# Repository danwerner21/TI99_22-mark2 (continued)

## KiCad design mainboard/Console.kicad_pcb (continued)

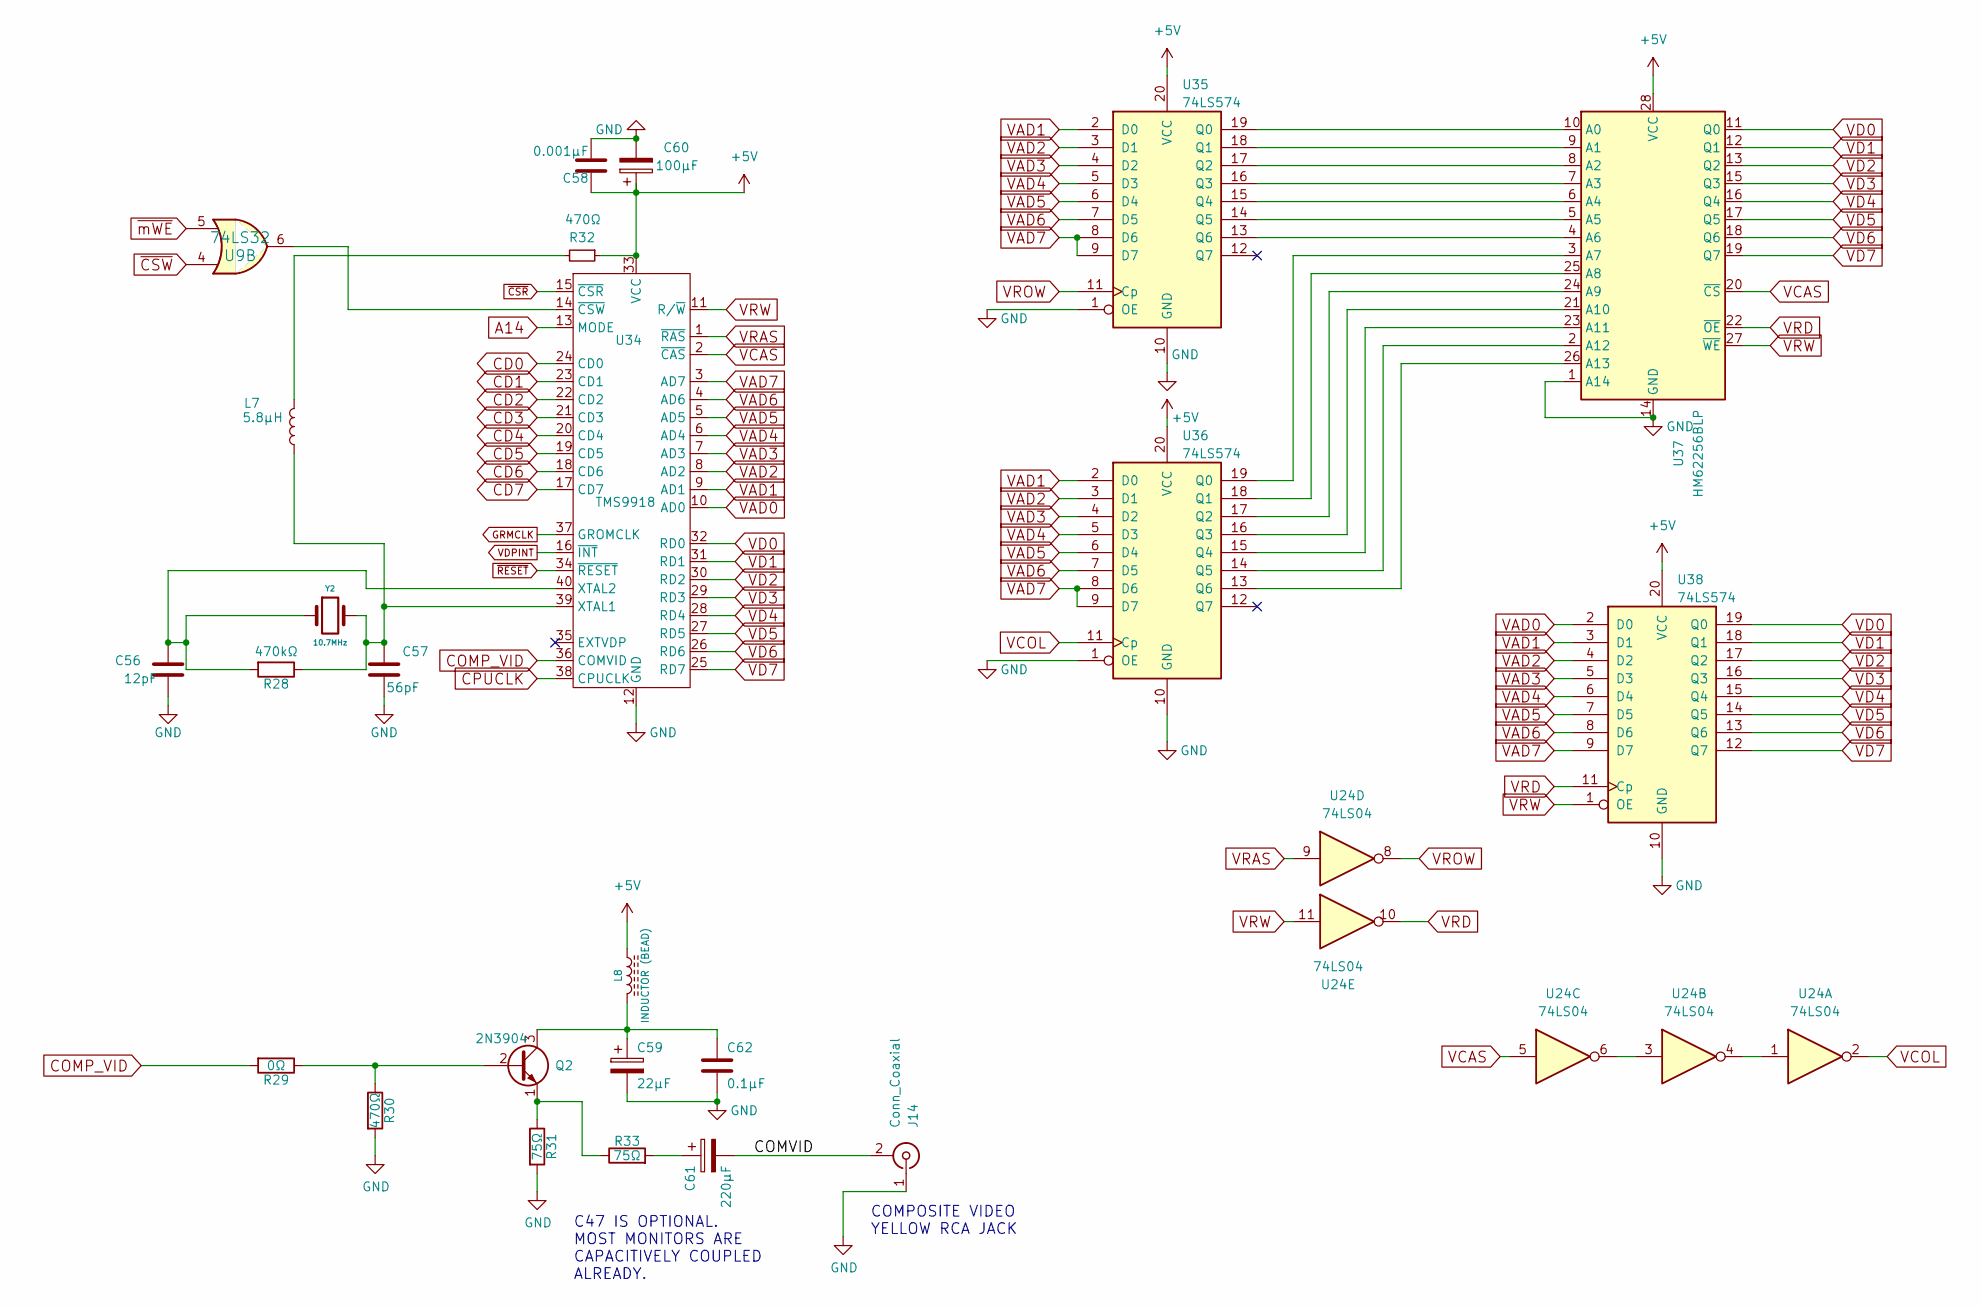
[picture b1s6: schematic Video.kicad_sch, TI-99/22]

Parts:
C56: 12pF; STD_DDW_CAP
C57: 56pF; STD_DDW_CAP
C58: 0.001µF; STD_DDW_CAP
C59: 22µF; STD_DDW_PCAP
C60: 100µF; STD_DDW_PCAP
C61: 220µF; STD_DDW_PCAP
C62: 0.1µF; STD_DDW_CAP
J14: Conn_Coaxial; CUI_RCJ-047
L7: 5.8µH; STD_DDW_RESISTOR
L8: INDUCTOR (BEAD); STD_DDW_RESISTOR
Q2: 2N3904; STD_DDW_TO92
R28: 470kΩ; STD_DDW_RESISTOR
R29: 0Ω; STD_DDW_RESISTOR
R30, R32: 470Ω; STD_DDW_RESISTOR
R31, R33: 75Ω; STD_DDW_RESISTOR
U9: 74LS32; STD_DDW_DIP14
U24: 74LS04; STD_DDW_DIP14
U34: TMS9918; STD_DDW_DIP40
U35, U36, U38: 74LS574; STD_DDW_DIP20
U37: HM62256BLP; STD_DDW_DIP28
Y2: 10.7MHz; STD_DDW_XTAL

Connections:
+5V: C58.1, C60.1, L8.1, R32.1, U34.33 (VCC), U35.20 (VCC), U36.20 (VCC), U37.28 (VCC), U38.20 (VCC); also elsewhere on the board
/Video/COMVID: C61.2, J14.2 (Ext)
A14: U34.13 (MODE); also elsewhere on the board
CD0: U34.24 (CD0); also elsewhere on the board
CD1: U34.23 (CD1); also elsewhere on the board
CD2: U34.22 (CD2); also elsewhere on the board
CD3: U34.21 (CD3); also elsewhere on the board
CD4: U34.20 (CD4); also elsewhere on the board
CD5: U34.19 (CD5); also elsewhere on the board
CD6: U34.18 (CD6); also elsewhere on the board
CD7: U34.17 (CD7); also elsewhere on the board
COMP_VID: R29.2, U34.36 (COMVID)
CPUCLK: U34.38 (CPUCLK); also elsewhere on the board
GND: C56.2, C57.2, C58.2, C59.2, C60.2, C62.2, J14.1 (In), R30.2, R31.2, U34.12 (GND), U35.1 (OE), U35.10 (GND), U36.1 (OE), U36.10 (GND), U37.1 (A14), U37.14 (GND), U38.10 (GND); also elsewhere on the board
GRMCLK: U34.37 (GROMCLK); also elsewhere on the board
unnamed: C61.1, R33.2
unnamed: L7.2, R32.2
unnamed: Q2.2 (B), R29.1, R30.1
unnamed: C59.1, C62.1, L8.2, Q2.3 (C)
unnamed: Q2.1 (E), R31.1, R33.1
unnamed: U24.1, U24.4
unnamed: U24.3, U24.6
unnamed: C57.1, L7.1, R28.1, U34.39 (XTAL1), Y2.2
unnamed: C56.1, R28.2, U34.40 (XTAL2), Y2.1
unnamed: U9.6, U34.14 (~CSW)
unnamed: U35.19 (Q0), U37.10 (A0)
unnamed: U35.18 (Q1), U37.9 (A1)
unnamed: U35.17 (Q2), U37.8 (A2)
unnamed: U35.16 (Q3), U37.7 (A3)
unnamed: U35.15 (Q4), U37.6 (A4)
unnamed: U35.14 (Q5), U37.5 (A5)
unnamed: U35.13 (Q6), U37.4 (A6)
unnamed: U36.19 (Q0), U37.3 (A7)
unnamed: U36.18 (Q1), U37.25 (A8)
unnamed: U36.17 (Q2), U37.24 (A9)
unnamed: U36.16 (Q3), U37.21 (A10)
unnamed: U36.15 (Q4), U37.23 (A11)
unnamed: U36.14 (Q5), U37.2 (A12)
unnamed: U36.13 (Q6), U37.26 (A13)
VAD0: U34.10 (AD0), U38.2 (D0)
VAD1: U34.9 (AD1), U35.2 (D0), U36.2 (D0), U38.3 (D1)
VAD2: U34.8 (AD2), U35.3 (D1), U36.3 (D1), U38.4 (D2)
VAD3: U34.7 (AD3), U35.4 (D2), U36.4 (D2), U38.5 (D3)
VAD4: U34.6 (AD4), U35.5 (D3), U36.5 (D3), U38.6 (D4)
VAD5: U34.5 (AD5), U35.6 (D4), U36.6 (D4), U38.7 (D5)
VAD6: U34.4 (AD6), U35.7 (D5), U36.7 (D5), U38.8 (D6)
VAD7: U34.3 (AD7), U35.8 (D6), U35.9 (D7), U36.8 (D6), U36.9 (D7), U38.9 (D7)
VCAS: U24.5, U34.2 (~CAS), U37.20 (~CS)
VCOL: U24.2, U36.11 (Cp)
VD0: U34.32 (RD0), U37.11 (Q0), U38.19 (Q0)
VD1: U34.31 (RD1), U37.12 (Q1), U38.18 (Q1)
VD2: U34.30 (RD2), U37.13 (Q2), U38.17 (Q2)
VD3: U34.29 (RD3), U37.15 (Q3), U38.16 (Q3)
VD4: U34.28 (RD4), U37.16 (Q4), U38.15 (Q4)
VD5: U34.27 (RD5), U37.17 (Q5), U38.14 (Q5)
VD6: U34.26 (RD6), U37.18 (Q6), U38.13 (Q6)
VD7: U34.25 (RD7), U37.19 (Q7), U38.12 (Q7)
VDPINT: U34.16 (~INT); also elsewhere on the board
VRAS: U24.9, U34.1 (~RAS)
VRD: U24.10, U37.22 (~OE), U38.11 (Cp)
VROW: U24.8, U35.11 (Cp)
VRW: U24.11, U34.11 (R/~W), U37.27 (~WE), U38.1 (OE)
~CSR: U34.15 (~CSR); also elsewhere on the board
~CSW: U9.4; also elsewhere on the board
~RESET: U34.34 (~RESET); also elsewhere on the board
~mWE: U9.5; also elsewhere on the board

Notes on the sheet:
COMPOSITE VIDEO YELLOW RCA JACK
C47 IS OPTIONAL. MOST MONITORS ARE CAPACITIVELY COUPLED ALREADY.

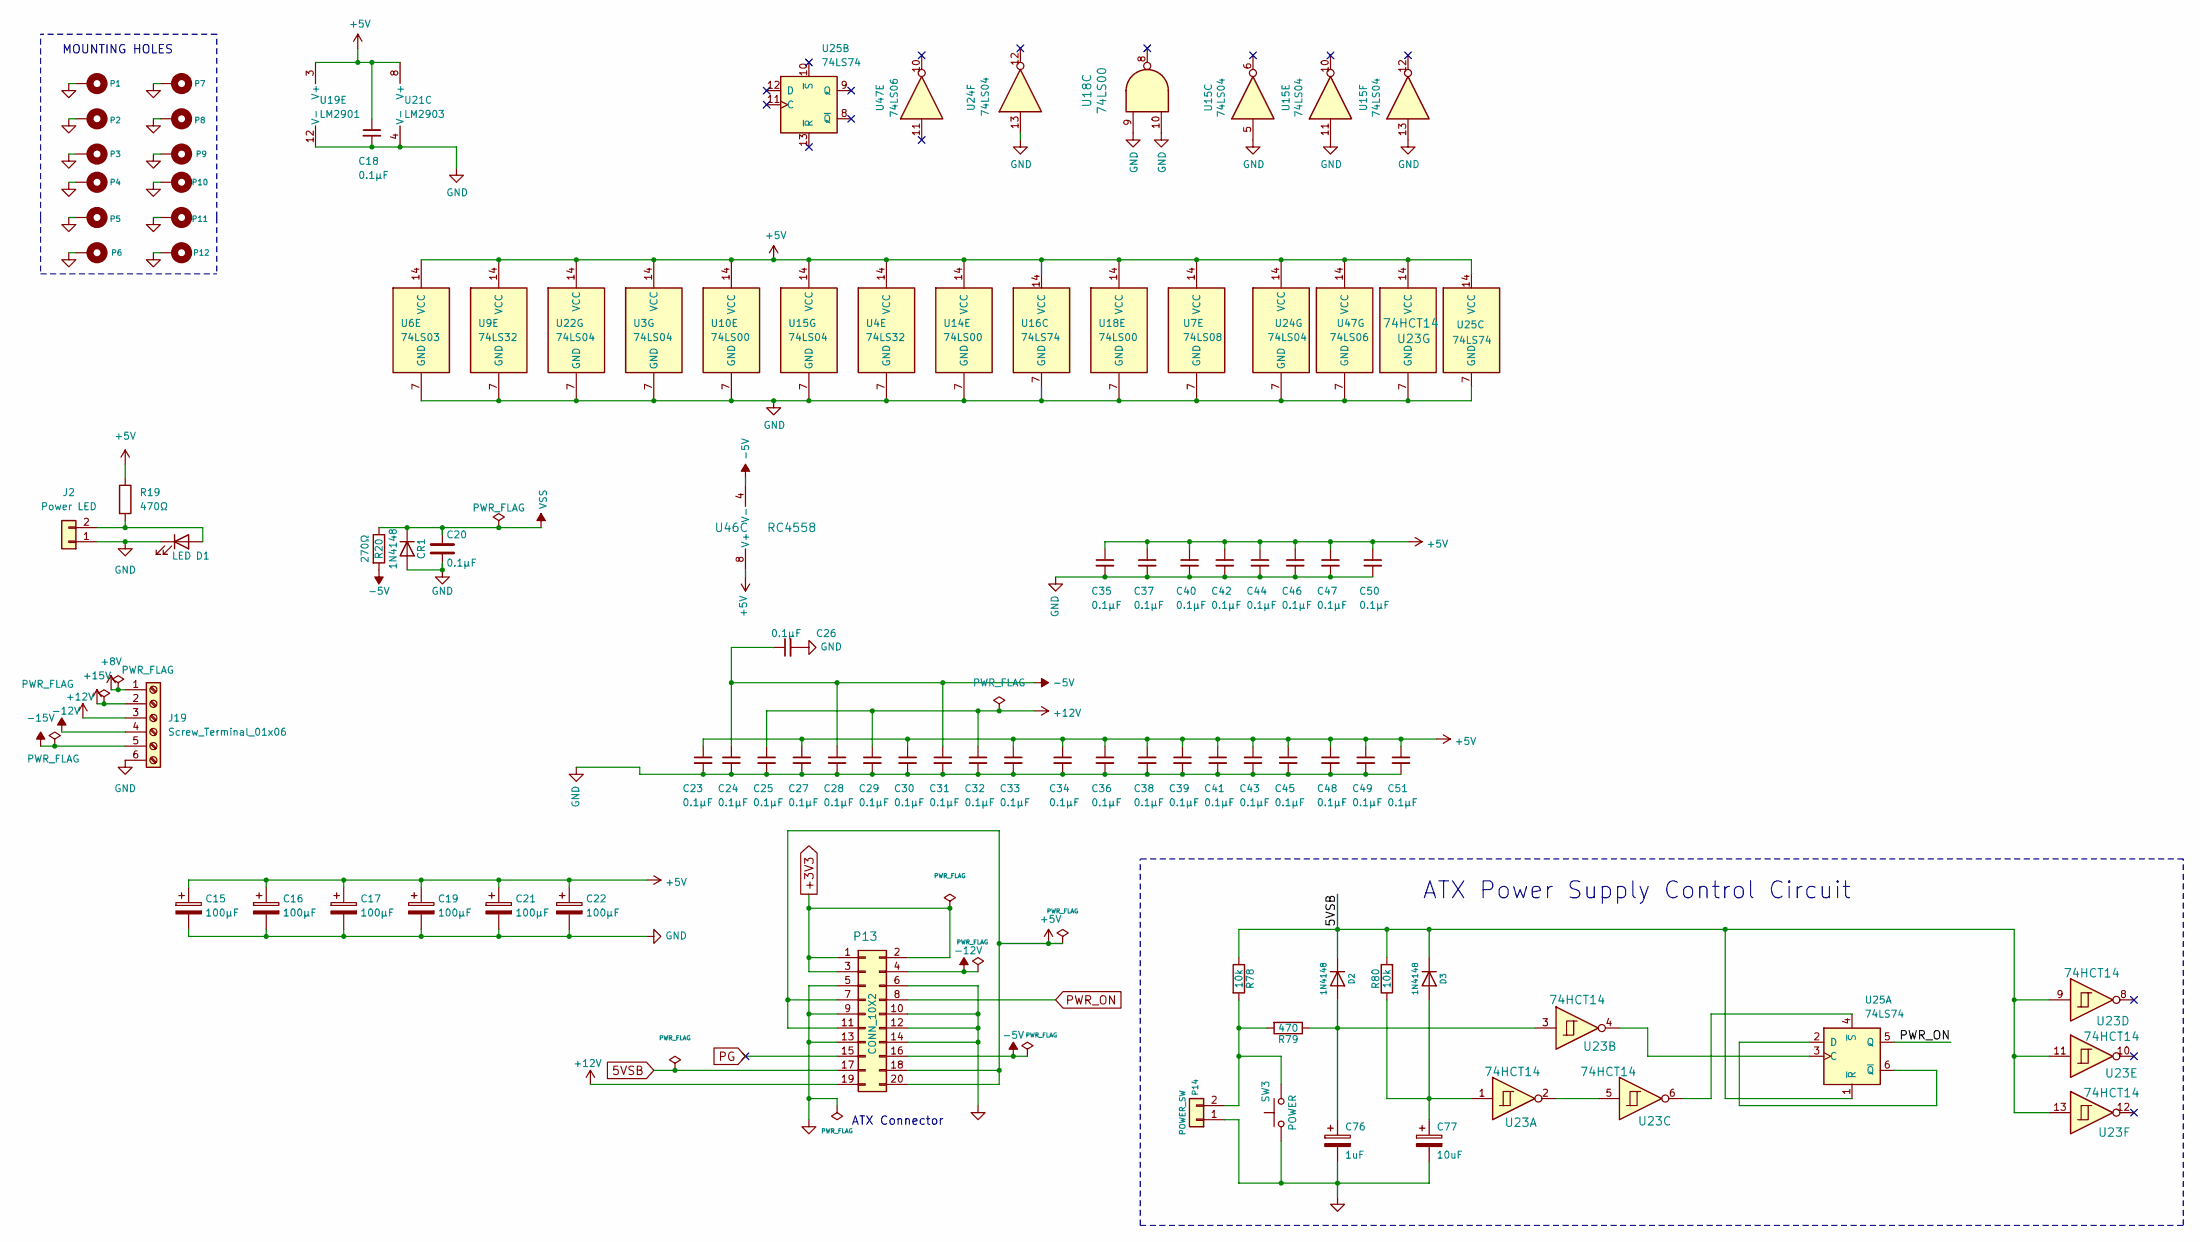
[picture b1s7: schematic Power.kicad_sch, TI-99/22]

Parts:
C15, C16, C17, C19, C21, C22: 100µF; STD_DDW_PCAP
C18, C20, C23, C24, C25, C26, C27, C28, C29, C30, C31, C32, C33, C34, C35, C36, C37, C38, C39, C40, C41, C42, C43, C44, C45, C46, C47, C48, C49, C50, C51: 0.1µF; STD_DDW_CAP
C76: 1uF; STD_DDW_PCAP
C77: 10uF; STD_DDW_PCAP
CR1: 1N4148; STD_DDW_DIODE
D1: LED; STD_DDW_LED5
D2, D3: 1N4148; STD_DDW_DIODE
J2: Power LED; STD_DDW_PINHEAD_V_1x02
J19: Screw_Terminal_01x06; TerminalBlock_RND_205-00005_1x06_P5.00mm_Horizontal
P1, P2, P3, P4, P5, P6, P7, P8, P9, P10, P11, P12: CONN_1; MountingHole_3.2mm_M3_Pad_TopBottom
P13: CONN_10X2; ATXConnector
P14: POWER_SW; STD_DDW_PINHEAD_V_1x02
R19: 470Ω; STD_DDW_RESISTOR
R20: 270Ω; STD_DDW_RESISTOR
R78, R80: 10k; STD_DDW_RESISTOR
R79: 470; STD_DDW_RESISTOR
SW3: POWER; STD_DDW_TACTSW
U3, U15, U22, U24: 74LS04; STD_DDW_DIP14
U4, U9: 74LS32; STD_DDW_DIP14
U6: 74LS03; STD_DDW_DIP14
U7: 74LS08; STD_DDW_DIP14
U10, U14, U18: 74LS00; STD_DDW_DIP14
U16, U25: 74LS74; STD_DDW_DIP14
U19: LM2901; STD_DDW_DIP14
U21: LM2903; STD_DDW_DIP8
U23: 74HCT14; STD_DDW_DIP14
U46: RC4558; STD_DDW_DIP8
U47: 74LS06; STD_DDW_DIP14

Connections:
5VSB: D2.1 (K), D3.1 (K), P13.17, R78.1, R80.2, U23.9, U23.11, U23.13, U25.1 (~R)
+3V3: P13.1, P13.2, P13.3
+5V: C15.1, C16.1, C17.1, C18.1, C19.1, C21.1, C22.1, C23.1, C27.1, C30.1, C33.1, C34.1, C35.1, C36.1, C37.1, C38.1, C39.1, C40.1, C41.1, C42.1, C43.1, C44.1, C45.1, C46.1, C47.1, C48.1, C49.1, C50.1, C51.1, P13.7, P13.11, P13.18, P13.20, R19.1, U3.14 (VCC), U4.14 (VCC), U6.14 (VCC), U7.14 (VCC), U9.14 (VCC), U10.14 (VCC), U14.14 (VCC), U15.14 (VCC), U16.14 (VCC), U18.14 (VCC), U19.3 (V+), U21.8 (V+), U22.14 (VCC), U23.14 (VCC), U24.14 (VCC), U25.14 (VCC), U46.8 (V+), U47.14 (VCC); also elsewhere on the board
+8V: J19.1; also elsewhere on the board
+12V: C25.1, C29.1, C32.1, J19.3, P13.19; also elsewhere on the board
+15V: J19.2; also elsewhere on the board
-5V: C24.1, C26.1, C28.1, C31.1, P13.16, R20.2, U46.4 (V-); also elsewhere on the board
-12V: J19.4, P13.4
-15V: J19.5; also elsewhere on the board
GND: C15.2, C16.2, C17.2, C18.2, C19.2, C20.2, C21.2, C22.2, C23.2, C24.2, C25.2, C26.2, C27.2, C28.2, C29.2, C30.2, C31.2, C32.2, C33.2, C34.2, C35.2, C36.2, C37.2, C38.2, C39.2, C40.2, C41.2, C42.2, C43.2, C44.2, C45.2, C46.2, C47.2, C48.2, C49.2, C50.2, C51.2, C76.2, C77.2, CR1.2 (A), D1.1 (K), J2.1, J19.6, P1.1, P2.1, P3.1, P4.1, P5.1, P6.1, P7.1, P8.1, P9.1, P10.1, P11.1, P12.1, P13.5, P13.6, P13.9, P13.10, P13.12, P13.13, P13.14, P14.1, SW3.1, U3.7 (GND), U4.7 (GND), U6.7 (GND), U7.7 (GND), U9.7 (GND), U10.7 (GND), U14.7 (GND), U15.5, U15.7 (GND), U15.11, U15.13, U16.7 (GND), U18.7 (GND), U18.9, U18.10, U19.12 (V-), U21.4 (V-), U22.7 (GND), U23.7 (GND), U24.7 (GND), U24.13, U25.7 (GND), U47.7 (GND); also elsewhere on the board
unnamed: D1.2 (A), J2.2, R19.2
unnamed: C76.1, D2.2 (A), R79.1, U23.3
unnamed: C77.1, D3.2 (A), R80.1, U23.1
unnamed: P14.2, R78.2, R79.2, SW3.2
unnamed: U23.2, U23.5
unnamed: U23.4, U25.3 (C)
unnamed: U25.2 (D), U25.6 (~Q)
unnamed: U23.6, U25.4 (~S)
PG: P13.15
PWR_ON: P13.8, U25.5 (Q)
VSS: C20.1, CR1.1 (K), R20.1; also elsewhere on the board

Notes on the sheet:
ATX Power Supply Control Circuit
MOUNTING HOLES
ATX Connector

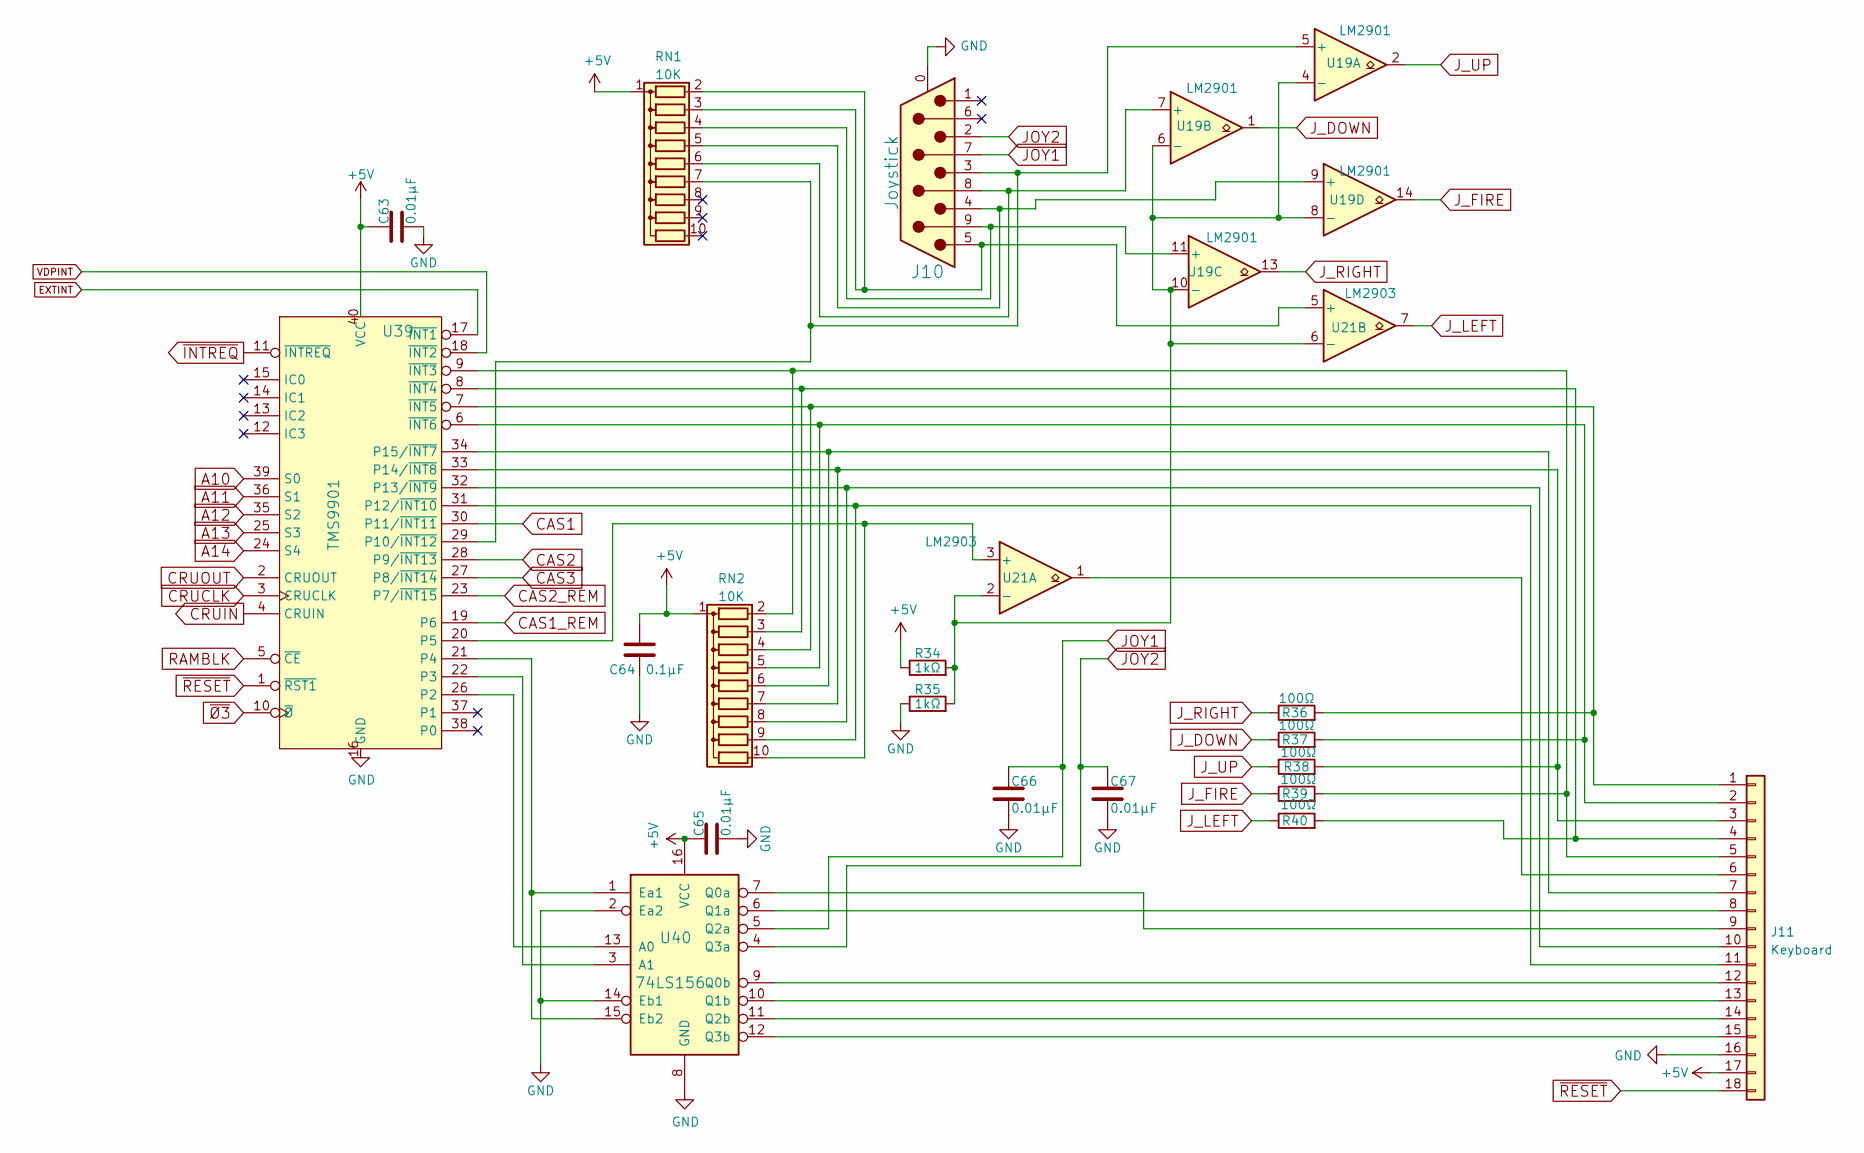
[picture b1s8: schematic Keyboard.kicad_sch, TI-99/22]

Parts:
C63, C65, C66, C67: 0.01µF; STD_DDW_CAP
C64: 0.1µF; STD_DDW_CAP
J10: Joystick; STD_DDW_DSUB9_MALE
J11: Keyboard; STD_DDW_PINHEAD_V_1x18
R34, R35: 1kΩ; STD_DDW_RESISTOR
R36, R37, R38, R39, R40: 100Ω; STD_DDW_RESISTOR
RN1, RN2: 10K; STD_DDW_SIP10
U19: LM2901; STD_DDW_DIP14
U21: LM2903; STD_DDW_DIP8
U39: TMS9901; STD_DDW_DIP40
U40: 74LS156; STD_DDW_DIP16

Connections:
+5V: C63.1, C64.2, C65.1, J11.17, R34.1, RN1.1 (common), RN2.1 (common), U39.40 (VCC), U40.16 (VCC); also elsewhere on the board
A10: U39.39 (S0); also elsewhere on the board
A11: U39.36 (S1); also elsewhere on the board
A12: U39.35 (S2); also elsewhere on the board
A13: U39.25 (S3); also elsewhere on the board
A14: U39.24 (S4); also elsewhere on the board
CAS1: U39.30 (P11/~INT11); also elsewhere on the board
CAS1_REM: U39.19 (P6); also elsewhere on the board
CAS2: U39.28 (P9/~INT13); also elsewhere on the board
CAS2_REM: U39.23 (P7/~INT15); also elsewhere on the board
CAS3: U39.27 (P8/~INT14); also elsewhere on the board
CRUCLK: U39.3 (CRUCLK); also elsewhere on the board
CRUIN: U39.4 (CRUIN); also elsewhere on the board
CRUOUT: U39.2 (CRUOUT); also elsewhere on the board
EXTINT: U39.17 (~INT1); also elsewhere on the board
GND: C63.2, C64.1, C65.2, C66.2, C67.2, J10.0 (PAD), J11.16, R35.1, U39.16 (GND), U40.2 (Ea2), U40.8 (GND), U40.14 (Eb1); also elsewhere on the board
JOY1: C66.1, J10.7, U40.5 (Q2a)
JOY2: C67.1, J10.2, U40.4 (Q3a)
J_DOWN: R37.1, U19.1
J_FIRE: R39.1, U19.14
J_LEFT: R40.1, U21.7
J_RIGHT: R36.1, U19.13
J_UP: R38.1, U19.2
unnamed: J11.1, R36.2, RN2.4 (R3), U39.7 (~INT5)
unnamed: J11.2, R37.2, RN2.5 (R4), U39.6 (~INT6)
unnamed: J11.3, R38.2, RN2.7 (R6), U39.33 (P14/~INT8)
unnamed: J11.4, R40.2, RN2.3 (R2), U39.8 (~INT4)
unnamed: J11.5, R39.2, RN2.2 (R1), U39.9 (~INT3)
unnamed: J11.6, U21.1
unnamed: J11.7, RN2.6 (R5), U39.34 (P15/~INT7)
unnamed: J11.8, U40.6 (Q1a)
unnamed: J11.9, U40.7 (Q0a)
unnamed: J11.10, RN2.8 (R7), U39.32 (P13/~INT9)
unnamed: J11.11, RN2.9 (R8), U39.31 (P12/~INT10)
unnamed: J11.12, U40.9 (Q0b)
unnamed: J11.13, U40.10 (Q1b)
unnamed: J11.14, U40.11 (Q2b)
unnamed: J11.15, U40.12 (Q3b)
unnamed: J10.5, RN1.2 (R1), RN1.3 (R2), U21.5 (+)
unnamed: J10.9, RN1.4 (R3), U19.11 (+)
unnamed: J10.4, RN1.5 (R4), U19.9 (+)
unnamed: J10.8, RN1.6 (R5), U19.7 (+)
unnamed: J10.3, RN1.7 (R6), U19.5 (+), U39.29 (P10/~INT12)
unnamed: RN2.10 (R9), U21.3 (+), U39.20 (P5)
unnamed: R34.2, R35.2, U19.4 (-), U19.6 (-), U19.8 (-), U19.10 (-), U21.2 (-), U21.6 (-)
unnamed: U39.26 (P2), U40.13 (A0)
unnamed: U39.22 (P3), U40.3 (A1)
unnamed: U39.21 (P4), U40.1 (Ea1), U40.15 (Eb2)
RAMBLK: U39.5 (~CE); also elsewhere on the board
VDPINT: U39.18 (~INT2); also elsewhere on the board
~INTREQ: U39.11 (~INTREQ); also elsewhere on the board
~RESET: J11.18, U39.1 (~RST1); also elsewhere on the board
~Ø3: U39.10 (~Ø); also elsewhere on the board

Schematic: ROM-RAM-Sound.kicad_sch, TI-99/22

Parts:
C53: 100µF; STD_DDW_PCAP
C54, C55: 0.1µF; STD_DDW_CAP
J5, J6: ROM Select; STD_DDW_PINHEAD_V_1x03
J7: Sound Clock Select; STD_DDW_PINHEAD_V_1x03
J9: Conn_Coaxial; CUI_RCJ-047
R27: 10Ω; STD_DDW_RESISTOR
U29, U30: HM62256BLP; STD_DDW_DIP28
U31, U32: 27C64; STD_DDW_DIP28
U33: SN76489; STD_DDW_DIP16

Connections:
+5V: C55.2, J5.1, J6.1, U29.28 (VCC), U30.28 (VCC), U31.27 (~PGM), U31.28 (VCC), U32.27 (~PGM), U32.28 (VCC), U33.16 (VCC); also elsewhere on the board
A0: U29.10 (A0), U30.10 (A0); also elsewhere on the board
A1: U29.9 (A1), U30.9 (A1); also elsewhere on the board
A2: U29.8 (A2), U30.8 (A2); also elsewhere on the board
A3: U29.7 (A3), U30.7 (A3), U31.23 (A11), U32.23 (A11); also elsewhere on the board
A4: U29.6 (A4), U30.6 (A4), U31.21 (A10), U32.21 (A10); also elsewhere on the board
A5: U29.5 (A5), U30.5 (A5), U31.24 (A9), U32.24 (A9); also elsewhere on the board
A6: U29.4 (A6), U30.4 (A6), U31.25 (A8), U32.25 (A8); also elsewhere on the board
A7: U29.3 (A7), U30.3 (A7), U31.3 (A7), U32.3 (A7); also elsewhere on the board
A8: U29.25 (A8), U30.25 (A8), U31.4 (A6), U32.4 (A6); also elsewhere on the board
A9: U29.24 (A9), U30.24 (A9), U31.5 (A5), U32.5 (A5); also elsewhere on the board
A10: U29.21 (A10), U30.21 (A10), U31.6 (A4), U32.6 (A4); also elsewhere on the board
A11: U29.23 (A11), U30.23 (A11), U31.7 (A3), U32.7 (A3); also elsewhere on the board
A12: U29.2 (A12), U30.2 (A12), U31.8 (A2), U32.8 (A2); also elsewhere on the board
A13: U29.26 (A13), U30.26 (A13), U31.9 (A1), U32.9 (A1); also elsewhere on the board
A14: U29.1 (A14), U30.1 (A14), U31.10 (A0), U32.10 (A0); also elsewhere on the board
CD0: U29.11 (Q0), U31.19 (D7); also elsewhere on the board
CD1: U29.12 (Q1), U31.18 (D6); also elsewhere on the board
CD2: U29.18 (Q6), U31.17 (D5); also elsewhere on the board
CD3: U29.16 (Q4), U31.16 (D4); also elsewhere on the board
CD4: U29.17 (Q5), U31.15 (D3); also elsewhere on the board
CD5: U29.15 (Q3), U31.13 (D2); also elsewhere on the board
CD6: U29.13 (Q2), U31.12 (D1); also elsewhere on the board
CD7: U29.19 (Q7), U31.11 (D0); also elsewhere on the board
CD8: U30.15 (Q3), U32.19 (D7); also elsewhere on the board
CD9: U30.13 (Q2), U32.18 (D6); also elsewhere on the board
CD10: U30.12 (Q1), U32.17 (D5); also elsewhere on the board
CD11: U30.11 (Q0), U32.16 (D4); also elsewhere on the board
CD12: U30.19 (Q7), U32.15 (D3); also elsewhere on the board
CD13: U30.18 (Q6), U32.13 (D2); also elsewhere on the board
CD14: U30.17 (Q5), U32.12 (D1); also elsewhere on the board
CD15: U30.16 (Q4), U32.11 (D0); also elsewhere on the board
CPUCLK: J7.1; also elsewhere on the board
D0: U33.3 (D0); also elsewhere on the board
D1: U33.2 (D1); also elsewhere on the board
D2: U33.1 (D2); also elsewhere on the board
D3: U33.15 (D3); also elsewhere on the board
D4: U33.13 (D4); also elsewhere on the board
D5: U33.12 (D5); also elsewhere on the board
D6: U33.11 (D6); also elsewhere on the board
D7: U33.10 (D7); also elsewhere on the board
GND: C55.1, J5.3, J6.3, J9.1 (In), R27.2, U29.14 (GND), U29.22 (~OE), U30.14 (GND), U30.22 (~OE), U31.14 (GND), U31.22 (~OE), U32.14 (GND), U32.22 (~OE), U33.8 (GND); also elsewhere on the board
GRMCLK: J7.3; also elsewhere on the board
unnamed: C54.2, R27.1
unnamed: J5.2, U31.2 (A12)
unnamed: J6.2, U32.2 (A12)
unnamed: C53.1, C54.1, U33.7 (AOUT)
READY_~HOLD: U33.4 (READY); also elsewhere on the board
SNDIN: U33.9 (AIN); also elsewhere on the board
SNDOUT: C53.2, J9.2 (Ext)
SOUNDCLK: J7.2, U33.14 (CLK)
~RAM: U29.20 (~CS), U30.20 (~CS); also elsewhere on the board
~ROM: U31.20 (~CE), U32.20 (~CE); also elsewhere on the board
~SOUND_SEL: U33.6 (~CE); also elsewhere on the board
~WE: U29.27 (~WE), U30.27 (~WE); also elsewhere on the board
~mWE: U33.5 (~WE); also elsewhere on the board

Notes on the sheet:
AUDIO RED RCA JACK

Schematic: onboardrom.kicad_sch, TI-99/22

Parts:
J16: Rom Select 1; STD_DDW_PINHEAD_V_1x03
J17: Rom Select 2; STD_DDW_PINHEAD_V_1x03
R57: 10kΩ; STD_DDW_RESISTOR
SW2: Internal Cart ROM Enable; STD_DDW_PINHEAD_V_1x02
U44: 74LS379; STD_DDW_DIP16
U45: 27C010-C; STD_DDW_DIP32

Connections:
+5V: R57.1, U44.16 (VCC), U45.31 (~PGM), U45.32 (VCC); also elsewhere on the board
A3: U45.4 (A12); also elsewhere on the board
A4: U45.25 (A11); also elsewhere on the board
A5: U45.23 (A10); also elsewhere on the board
A6: U45.26 (A9); also elsewhere on the board
A7: U45.27 (A8); also elsewhere on the board
A8: U45.5 (A7); also elsewhere on the board
A9: U45.6 (A6); also elsewhere on the board
A10: U45.7 (A5); also elsewhere on the board
A11: U44.13 (D3), U45.8 (A4); also elsewhere on the board
A12: U44.12 (D2), U45.9 (A3); also elsewhere on the board
A13: U44.5 (D1), U45.10 (A2); also elsewhere on the board
A15-CRUOUT: U45.12 (A0); also elsewhere on the board
D0: U45.21 (D7); also elsewhere on the board
D1: U45.20 (D6); also elsewhere on the board
D2: U45.19 (D5); also elsewhere on the board
D3: U45.18 (D4); also elsewhere on the board
D4: U45.17 (D3); also elsewhere on the board
D5: U45.15 (D2); also elsewhere on the board
D6: U45.14 (D1); also elsewhere on the board
D7: U45.13 (D0); also elsewhere on the board
GND: J16.1, J17.1, U44.8 (GND), U45.1 (VPP), U45.16 (GND), U45.22 (~CE); also elsewhere on the board
IO_A14: U44.4 (D0), U45.11 (A1); also elsewhere on the board
IR_A1: J17.3, U44.10 (Q2)
IR_A1_O: J17.2, U45.3 (A15)
IR_A2: J16.3, U44.7 (Q1)
IR_A2_O: J16.2, U45.29 (A14)
unnamed: U44.2 (Q0), U45.28 (A13)
unnamed: U44.15 (Q3), U45.2 (A16)
~IROMG: R57.2, SW2.2, U44.1 (~E), U45.24 (~OE)
~ROMG: SW2.1; also elsewhere on the board
~mWE: U44.9 (CP); also elsewhere on the board

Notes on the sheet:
27C010 J17-2&3 J18-2&3 27C512 J17-2&3 J18-2&3 27C256 J17-1&2 J18-2&3 27C128 J17-1&2 J18-1&2 27C64 J17-1&2 J18-1&2

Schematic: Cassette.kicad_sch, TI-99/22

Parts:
C68, C71, C74: 0.1µF; STD_DDW_CAP
C69: 220pF; STD_DDW_CAP
C70: 0.022µF; STD_DDW_CAP
C72: 0.01µF; STD_DDW_CAP
C73, C75: 0.001µF; STD_DDW_CAP
CR4: 1N4148; STD_DDW_DIODE
J18: Cassette; STD_DDW_DSUB9_MALE
L10, L11, L12, L13, L14, L15, L16: 8.2µh; STD_DDW_RESISTOR
Q3, Q4: 2N4946 or TIS92; STD_DDW_TO92
R58, R60: 6.8kΩ; STD_DDW_RESISTOR
R59: 39kΩ; STD_DDW_RESISTOR
R61, R62, R67, R68: 1KΩ; STD_DDW_RESISTOR
R63: 120kΩ; STD_DDW_RESISTOR
R64: 2.7kΩ; STD_DDW_RESISTOR
R65, R66, R76: 220Ω; STD_DDW_RESISTOR
R69: 10KΩ; STD_DDW_RESISTOR
R70: 9.1kΩ; STD_DDW_RESISTOR
R71, R72: 10kΩ; STD_DDW_RESISTOR
R73, R75: 5.6kΩ; STD_DDW_RESISTOR
R74: 5.6KΩ; STD_DDW_RESISTOR
R77: 15Ω; STD_DDW_RESISTOR
U46: RC4558; STD_DDW_DIP8
U47: 74LS06; STD_DDW_DIP14
U48, U49: TIL119; STD_DDW_DIP6

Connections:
+5V: R67.2, R68.2, R70.2, U48.1 (A), U49.1 (A); also elsewhere on the board
CAS1: CR4.1 (K), R64.2; also elsewhere on the board
CAS1_REM: R62.2, U47.3; also elsewhere on the board
CAS2: U47.5; also elsewhere on the board
CAS2_REM: R61.2, U47.1; also elsewhere on the board
CAS3: U47.13; also elsewhere on the board
GND: C70.2, C71.2, C72.2, C74.2, C75.2, CR4.2 (A), J18.0 (PAD), L13.1, R61.1, R62.1, R73.1, R76.1, U46.2 (-), U46.5 (+); also elsewhere on the board
unnamed: C68.1, L14.1, R72.2
unnamed: C68.2, R58.2
unnamed: C69.2, R59.1, R60.2, U46.7
unnamed: C71.1, R71.2, R72.1, U47.12
unnamed: C72.1, C73.1, R69.1
unnamed: C73.2, R74.2
unnamed: C74.1, L15.1, R73.2, R75.2, R77.1
unnamed: C75.1, L12.1, R74.1, R76.2
unnamed: J18.1, L11.2
unnamed: J18.3, L13.2
unnamed: J18.4, L15.2
unnamed: J18.5, L12.2
unnamed: J18.6, L10.2
unnamed: J18.8, L14.2
unnamed: J18.9, L16.2
unnamed: L16.1, R77.2
unnamed: Q3.2 (B), U48.4 (KK)
unnamed: L10.1, Q3.3 (C), U48.5
unnamed: J18.7, Q3.1 (E)
unnamed: Q4.2 (B), U49.4 (KK)
unnamed: L11.1, Q4.3 (C), U49.5
unnamed: J18.2, Q4.1 (E)
unnamed: R63.1, R64.1, U46.1
unnamed: R65.1, U47.2
unnamed: R66.1, U47.4
unnamed: R67.1, U47.6, U47.9
unnamed: R68.1, R69.2, U47.8
unnamed: R70.1, R71.1, R75.1
unnamed: C70.1, R60.1, R63.2, U46.3 (+)
unnamed: C69.1, R58.1, R59.2, U46.6 (-)
unnamed: R65.2, U48.2 (K)
unnamed: R66.2, U49.2 (K)

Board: 2 copper layers, 269 parts (0 on the bottom side), 336 nets, no tracks yet.

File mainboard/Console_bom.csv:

Reference|Value|Datasheet|Footprint|Qty|DNP
C1,C9,C11,C58,C73,C75|0.001µF|~|Custom:STD_DDW_CAP|6|
C2|22pF|~|Custom:STD_DDW_CAP|1|
C3,C5,C59|22µF|~|Custom:STD_DDW_PCAP|3|
C4,C7,C13,C14,C18,C20,C23,C24,C25,C26,C27,C28,C29,C30,C31,C32,C33,C34,C35,C36,C37,C38,C39,C40,C41,C42,C43,C44,C45,C46,C47,C48,C49,C50,C51,C54,C55,C62,C64,C68,C71,C74|0.1µF|~|Custom:STD_DDW_CAP|42|
C6|1µF|~|Custom:STD_DDW_CAP|1|
C8,C12,C52,C63,C65,C66,C67,C72|0.01µF|~|Custom:STD_DDW_CAP|8|
C10,C15,C16,C17,C19,C21,C22,C53,C60|100µF|~|Custom:STD_DDW_PCAP|9|
C56|12pF|~|Custom:STD_DDW_CAP|1|
C57|56pF|~|Custom:STD_DDW_CAP|1|
C61|220µF|~|Custom:STD_DDW_PCAP|1|
C69|220pF|~|Custom:STD_DDW_CAP|1|
C70|0.022µF|~|Custom:STD_DDW_CAP|1|
C76|1uF|~|Custom:STD_DDW_PCAP|1|
C77|10uF|~|Custom:STD_DDW_PCAP|1|
CR1,CR4,D2,D3|1N4148|~|Custom:STD_DDW_DIODE|4|
CR2,CR3|1N914B|~|Custom:STD_DDW_DIODE|2|
D1|LED|~|Custom:STD_DDW_LED5|1|
J1,J3,J12,J13|Conn_02x30_Odd_Even|~|Custom:STD_DDW_CARDEDGE60|4|
J2|Power LED|~|Custom:STD_DDW_PINHEAD_V_1x02|1|
J4|UNICORN PORT|~|Custom:STD_DDW_PINHEAD_V_1x16|1|
J5,J6|ROM Select|~|Custom:STD_DDW_PINHEAD_V_1x03|2|
J7|Sound Clock Select|~|Custom:STD_DDW_PINHEAD_V_1x03|1|
J9,J14|Conn_Coaxial|~|Custom:CUI_RCJ-047|2|
J10|Joystick|~|Custom:STD_DDW_DSUB9_MALE|1|
J11|Keyboard|~|Custom:STD_DDW_PINHEAD_V_1x18|1|
J15|GROM Port||Custom:STD_DDW_PINHEAD_V_2x18|1|
J16|Rom Select 1|~|Custom:STD_DDW_PINHEAD_V_1x03|1|
J17|Rom Select 2|~|Custom:STD_DDW_PINHEAD_V_1x03|1|
J18|Cassette|~|Custom:STD_DDW_DSUB9_MALE|1|
J19|Screw_Terminal_01x06|~|TerminalBlock_RND:TerminalBlock_RND_205-00005_1x06_P5.00mm_Horizontal|1|
L1|0.33µH|~|Custom:STD_DDW_RESISTOR|1|
L7|5.8µH|~|Custom:STD_DDW_RESISTOR|1|
L8|INDUCTOR (BEAD)|~|Custom:STD_DDW_RESISTOR|1|
L10,L11,L12,L13,L14,L15,L16|8.2µh|~|Custom:STD_DDW_RESISTOR|7|
P13|CONN_10X2|~|Custom:ATXConnector|1|
P14|POWER_SW|~|Custom:STD_DDW_PINHEAD_V_1x02|1|
Q1|TIS92|~|Custom:STD_DDW_TO92|1|
Q2|2N3904|~|Custom:STD_DDW_TO92|1|
Q3,Q4|2N4946 or TIS92|~|Custom:STD_DDW_TO92|2|
R1|150kΩ|~|Custom:STD_DDW_RESISTOR|1|
R2,R9,R11,R18,R34,R35,R46|1kΩ|~|Custom:STD_DDW_RESISTOR|7|
R3|12kΩ|~|Custom:STD_DDW_RESISTOR|1|
R4|47kΩ|~|Custom:STD_DDW_RESISTOR|1|
R5,R6,R7,R8|22Ω|~|Custom:STD_DDW_RESISTOR|4|
R10,R26,R45,R54,R81,R83|4.7kΩ|~|Custom:STD_DDW_RESISTOR|6|
R12,R13,R14,R15,R16,R61,R62,R67,R68|1KΩ|~|Custom:STD_DDW_RESISTOR|9|
R17,R48,R50|2.2kΩ|~|Custom:STD_DDW_RESISTOR|3|
R19,R30,R32|470Ω|~|Custom:STD_DDW_RESISTOR|3|
R20|270Ω|~|Custom:STD_DDW_RESISTOR|1|
R21|1.5kΩ||Custom:STD_DDW_SIP10|1|
R22|361Ω|~|Custom:STD_DDW_RESISTOR|1|
R23,R73,R75|5.6kΩ|~|Custom:STD_DDW_RESISTOR|3|
R24,R27|10Ω|~|Custom:STD_DDW_RESISTOR|2|
R25|150Ω|~|Custom:STD_DDW_RESISTOR|1|
R28|470kΩ|~|Custom:STD_DDW_RESISTOR|1|
R29|0Ω|~|Custom:STD_DDW_RESISTOR|1|
R31,R33|75Ω|~|Custom:STD_DDW_RESISTOR|2|
R36,R37,R38,R39,R40,R51,R56,R82|100Ω|~|Custom:STD_DDW_RESISTOR|8|
R41,R42,R43,R44|62Ω|~|Custom:STD_DDW_RESISTOR|4|
R47|3.3kΩ|~|Custom:STD_DDW_RESISTOR|1|
R49,R52,R53,R55|330Ω|~|Custom:STD_DDW_RESISTOR|4|
R57,R71,R72|10kΩ|~|Custom:STD_DDW_RESISTOR|3|
R58,R60|6.8kΩ|~|Custom:STD_DDW_RESISTOR|2|
R59|39kΩ|~|Custom:STD_DDW_RESISTOR|1|
R63|120kΩ|~|Custom:STD_DDW_RESISTOR|1|
R64|2.7kΩ|~|Custom:STD_DDW_RESISTOR|1|
R65,R66,R76|220Ω|~|Custom:STD_DDW_RESISTOR|3|
R69|10KΩ|~|Custom:STD_DDW_RESISTOR|1|
R70|9.1kΩ|~|Custom:STD_DDW_RESISTOR|1|
R74|5.6KΩ|~|Custom:STD_DDW_RESISTOR|1|
R77|15Ω|~|Custom:STD_DDW_RESISTOR|1|
R78,R80|10k|~|Custom:STD_DDW_RESISTOR|2|
R79|470|~|Custom:STD_DDW_RESISTOR|1|
RN1,RN2|10K|http://www.vishay.com/docs/31509/csc.pdf|Custom:STD_DDW_SIP10|2|
SW1|RAM Size|~|Custom:STD_DDW_DIP10|1|
SW2|Internal Cart ROM Enable|~|Custom:STD_DDW_PINHEAD_V_1x02|1|
SW3|POWER|~|Custom:STD_DDW_TACTSW|1|
U1|TIM9904||Custom:STD_DDW_DIP20|1|
U2|TMS9900||Custom:STD_DDW_DIP64_WIDE|1|
U3,U15,U22,U24|74LS04|-- mixed values --|Custom:STD_DDW_DIP14|4|
U4,U9|74LS32|-- mixed values --|Custom:STD_DDW_DIP14|2|
U5,U8|74LS138||Custom:STD_DDW_DIP16|2|
U6|74LS03|-- mixed values --|Custom:STD_DDW_DIP14|1|
U7|74LS08|http://www.ti.com/lit/gpn/sn74LS08|Custom:STD_DDW_DIP14|1|
U10,U14,U18|74LS00|-- mixed values --|Custom:STD_DDW_DIP14|3|
U11,U20,U41,U42|74LS244||Custom:STD_DDW_DIP20|4|
U12|74LS373||Custom:STD_DDW_DIP20|1|
U13,U50|74LS245|-- mixed values --|Custom:STD_DDW_DIP20|2|
U16,U25|74LS74|-- mixed values --|Custom:STD_DDW_DIP14|2|
U17|74LS194||Custom:STD_DDW_DIP16|1|
U19|LM2901|https://www.st.com/resource/en/datasheet/lm2901.pdf|Custom:STD_DDW_DIP14|1|
U21|LM2903|http://www.ti.com/lit/ds/symlink/lm393.pdf|Custom:STD_DDW_DIP8|1|
U23|74HCT14|http://www.ti.com/lit/gpn/sn74LS14|Custom:STD_DDW_DIP14|1|
U26,U27,U28|TMC0430||Custom:STD_DDW_DIP16|3|
U29,U30,U37|HM62256BLP|https://web.mit.edu/6.115/www/document/62256.pdf|Custom:STD_DDW_DIP28|3|
U31,U32|27C64|http://ww1.microchip.com/downloads/en/DeviceDoc/11107M.pdf|Custom:STD_DDW_DIP28|2|
U33|SN76489||Custom:STD_DDW_DIP16|1|
U34|TMS9918||Custom:STD_DDW_DIP40|1|
U35,U36,U38|74LS574|http://www.ti.com/lit/gpn/sn74LS574|Custom:STD_DDW_DIP20|3|
U39|TMS9901||Custom:STD_DDW_DIP40|1|
U40|74LS156||Custom:STD_DDW_DIP16|1|
U44|74LS379|http://www.ti.com/lit/gpn/sn74LS379|Custom:STD_DDW_DIP16|1|
U45|27C010-C|http://ww1.microchip.com/downloads/en/DeviceDoc/doc0321.pdf|Custom:STD_DDW_DIP32|1|
U46|RC4558|http://www.ti.com/lit/ds/symlink/rc4558.pdf|Custom:STD_DDW_DIP8|1|
U47|74LS06|http://www.ti.com/lit/gpn/sn74LS06|Custom:STD_DDW_DIP14|1|
U48,U49|TIL119||Custom:STD_DDW_DIP6|2|
Y1|48.000 MHz|~|Custom:STD_DDW_XTAL|1|
Y2|10.7MHz|~|Custom:STD_DDW_XTAL|1|

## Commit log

2025-01-28 layout work
